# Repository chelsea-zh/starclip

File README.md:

# Starclip

This is a design for a set of hair accesories with incorporated LEDs. This uses the Adafruit Sparkle Motion Mini and WLED to respond to audio.

As of now, this is purely a design, so I have no final images. This will be a hand wired project.

This set consists of one large bow to be placed in the center of the back of the head, along with a star on each side. LEDs are placed around the edges of all parts. The stars are detachable.

## CAD
Made in Fusion 360:

Each part consists of a flat base and an extruded top that fit into each other.

## Wiring
Made in KiCad:

The project schematic is as follows:

While the majority of the project will be hand wired, the stars will be PCBs for ease of assembly.

In total, following a roughly half inch spacing between LEDs in the bow, there will be 18 LEDs in each half of the bow, wrapping around each wing and bottom tail. Each star will have 6 LEDs, ordered such that the light can move in a linear pattern across the star.

This project uses the Adafruit Sparkle Motion Mini, which as an incorporated I2S microphone and level shifters for 5V LEDs. This will be powered by a 3.7V 500mAh LiPo battery, connected to a Adafruit MiniBoost 5V through a JST connector. The switch is connected to the MiniBoost enable pin. 

As the Sparkle Motion Mini only has two output pins shifted to 5V for LEDs, the LED chains will be split per half, consisting of each half of the bow and continuing on to the star clips.

The star clips will be connected to the main bow through magnetic conectors at the bottom edge of the bow. This allows them to be detachable.

The connecting wiring will be visible, following a drooping pattern using white silicone wrapped wire.

## Assembly

Begin with the stars. The PCBs will fit into the star casing, with a cutout on one edge for the wires. The stars have rotational symmetry, which allows them to work for both the left and right side.

Attach all parts to the center bow base plate. There is a cutout on the top of the center piece for the slide switch, and cutouts on the bottom edge of each bow wing for the magnetic connectors. 

Once finished, place the top of the casing on in this order: tails, wings, center.

Attach crocodile clips or preferred type of hair clip.

## Firmware
This project uses [WLED.](https://kno.wled.ge/) This allows for audio responsive LEDs.

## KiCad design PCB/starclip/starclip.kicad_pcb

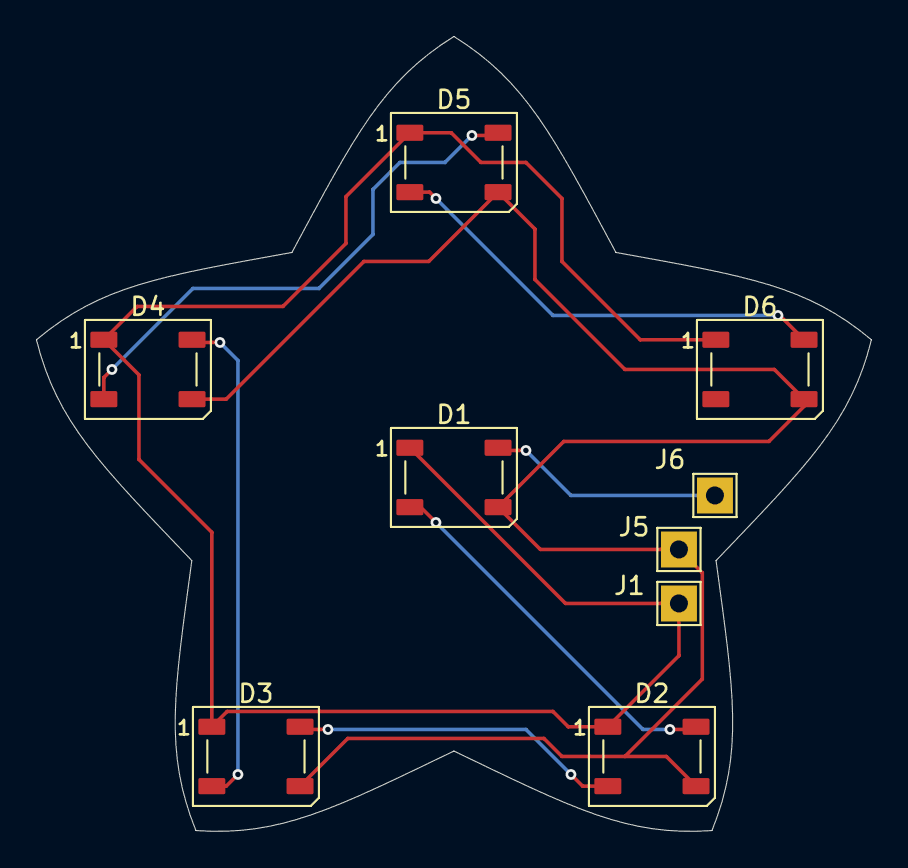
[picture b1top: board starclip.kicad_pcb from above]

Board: 2 copper layers, 46.4 x 44.2 mm, 9 parts (0 on the bottom side), 8 nets.

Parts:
D1, D2, D3, D4, D5, D6: WS2812B; LED_WS2812B_PLCC4_5.0x5.0mm_P3.2mm
J1, J5, J6: Conn_01x01_Pin; TestPoint_THTPad_2.0x2.0mm_Drill1.0mm

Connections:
unnamed: D1.4 (DIN), J6.1 (Pin_1_1)
unnamed: D1.2 (DOUT), D2.4 (DIN)
unnamed: D1.1 (VDD), D2.1 (VDD), D3.1 (VDD), D4.1 (VDD), D5.1 (VDD), D6.1 (VDD), J1.1 (Pin_1_1)
unnamed: D1.3 (VSS), D2.3 (VSS), D3.3 (VSS), D4.3 (VSS), D5.3 (VSS), D6.3 (VSS), J5.1 (Pin_1_1)
unnamed: D2.2 (DOUT), D3.4 (DIN)
unnamed: D3.2 (DOUT), D4.4 (DIN)
unnamed: D4.2 (DOUT), D5.4 (DIN)
unnamed: D5.2 (DOUT), D6.4 (DIN)
